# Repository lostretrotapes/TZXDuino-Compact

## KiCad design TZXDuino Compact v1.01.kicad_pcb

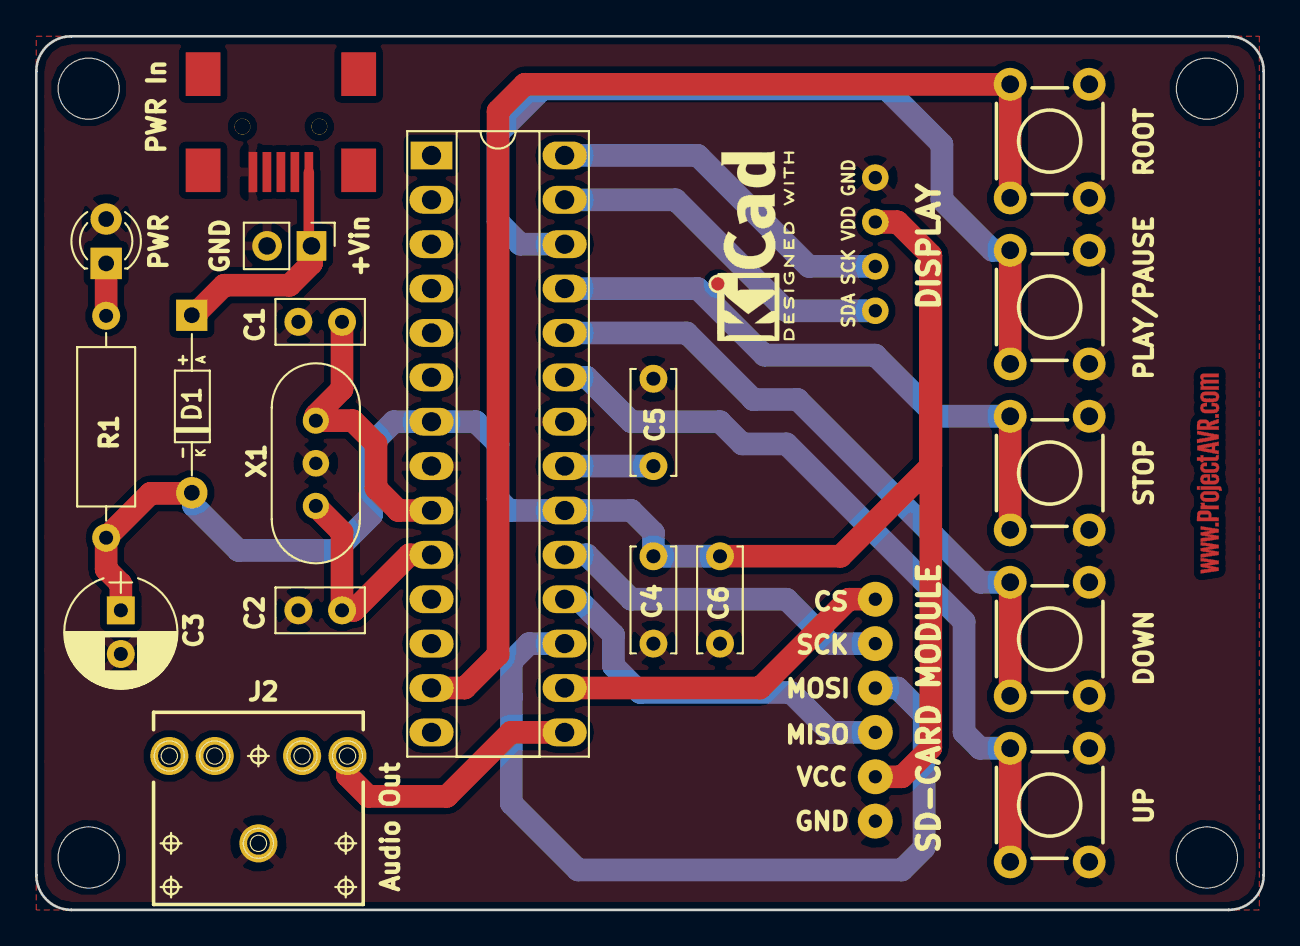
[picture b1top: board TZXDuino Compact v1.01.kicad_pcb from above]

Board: 2 copper layers, 70.2 x 50.0 mm, 21 parts (0 on the bottom side), 19 nets.

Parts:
C1, C2: 22pf; C_Disc_D5.0mm_W2.5mm_P2.50mm
C3: 10u; CP_Radial_D6.3mm_P2.50mm
C4, C5: 100n; C_Disc_D6.0mm_W2.5mm_P5.00mm
C6: 10n; C_Disc_D6.0mm_W2.5mm_P5.00mm
D1: DIODE; 1N4001_Diode_Case_59-10_Axial
D2: LED; LED_D3.0mm
DS1: OLED128x64; OLED128x64_I2C
IC1: ATMEGA328P-P; DIP-28_W7.62mm_Socket_LongPads_ZIF
J1: USB_MINI; USB-MINI-B-SMD
J2: 35RAPC4BHN2; 3.5-AUDIO-JACK-KIT
MOD1: Catalex_Micro_SD; Catalex_Micro-SD_Module
P1: CONN_2; Pin_Header_Straight_1x02_Pitch2.54mm
R1: 330R; R_Axial_DIN0309_L9.0mm_D3.2mm_P12.70mm_Horizontal
S1, S2, S3, S4, S5: TAC_SWITCH; TACTILE-PTH
X1: XTAL/RES 16MHz; XTAL-RES_HC49-4H_Vertical

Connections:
A0: IC1.23, S1.3, S1.4
A1: IC1.24, S2.3, S2.4
A2: IC1.25, S3.3, S3.4
A3: IC1.26, S4.3, S4.4
A4: DS1.4, IC1.27
A5: DS1.3, IC1.28
D7: IC1.13, S5.3, S5.4
D9: IC1.15, J2.2
D10: IC1.16, MOD1.4
GND: C1.1, C2.1, C3.2, C4.1, C5.2, C6.1, D2.2, DS1.1, IC1.8, IC1.22, J1.5, J2.1, MOD1.9, P1.2, S1.1, S1.2, S2.1, S2.2, S3.1, S3.2, S4.1, S4.2, S5.1, S5.2, X1.3
MISO: IC1.18, MOD1.7
MOSI: IC1.17, MOD1.6
unnamed: C5.1, IC1.21
unnamed: D2.1, R1.1
SCK: IC1.19, MOD1.5
VCC: C3.1, C4.2, C6.2, D1.2, DS1.2, IC1.7, IC1.20, MOD1.8, R1.2
VIN: D1.1, J1.1, P1.1
XTAL1: C1.2, IC1.9, X1.1
XTAL2: C2.2, IC1.10, X1.2

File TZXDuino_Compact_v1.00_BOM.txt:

TZXDuino Compact v1.00 Component List	
	
C1,C2		22pf
C3		10uf
C4,C5		100nf
C6		10nf
D2		LED 3.0mm
DS1		128x64 I2C OLED Display Module (Example: eBay-162473794373)
IC1		ATMEGA328P-P
J1		USB-MINI-B-SMD
P1		Pin_Header_Straight_1x02_Pitch 2.54mm
X1		XTAL/RES 16MHz
R1		330R
S1,S2,S3,S4,S5	Tac Switch
MOD1		Catalex_Micro-SD_Module (Example: eBay-262460777856)
J2		3.5-AUDIO-JACK
D1		1N4001
1x		6-way Dupont style socket
1x		4-way Dupont style socket
